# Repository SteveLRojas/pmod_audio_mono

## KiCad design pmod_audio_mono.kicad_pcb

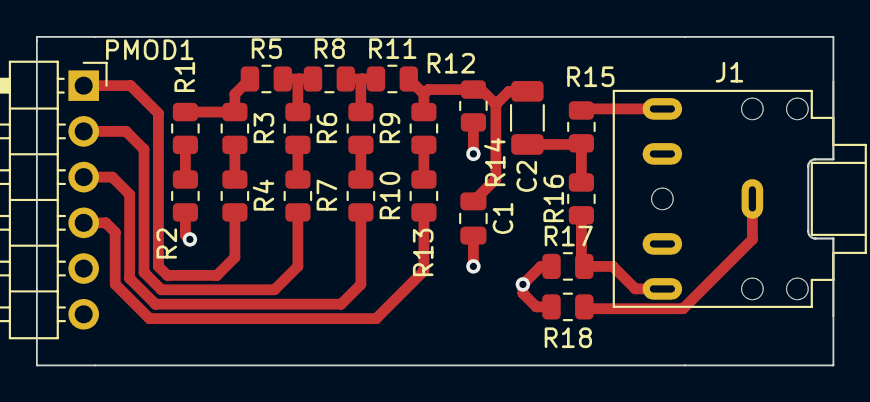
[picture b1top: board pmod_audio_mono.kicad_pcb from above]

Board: 2 copper layers, 44.2 x 18.2 mm, 22 parts (0 on the bottom side), 18 nets.

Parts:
C1: 1n; C_0805_2012Metric
C2: 106; C_1206_3216Metric
J1: AudioJack3_SwitchTR; Jack_3.5mm_CUI_SJ1-3525N_Horizontal
PMOD1: PMOD-Device-x1-Type-1-GPIO; pmod_type_1_pin
R1, R2, R3, R4, R5, R6, R7, R8, R9, R10, R11, R12, R13: 75; R_0805_2012Metric
R14: 1M; R_0805_2012Metric
R15, R16, R17, R18: 0; R_0805_2012Metric

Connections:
GND: C1.2, PMOD1.5 (GND), R2.2, R14.2, R17.1, R18.1
unnamed: C1.1, C2.1, R11.2, R12.1, R14.1
unnamed: C2.2, R15.1, R16.1
unnamed: J1.R, R16.2, R17.2
unnamed: J1.S, R18.2
unnamed: J1.T, R15.2
unnamed: PMOD1.1 (IO0), R4.2
unnamed: PMOD1.2 (IO1), R7.2
unnamed: PMOD1.3 (IO2), R10.2
unnamed: PMOD1.4 (IO3), R13.2
unnamed: R1.1, R3.1, R5.1
unnamed: R1.2, R2.1
unnamed: R3.2, R4.1
unnamed: R5.2, R6.1, R8.1
unnamed: R6.2, R7.1
unnamed: R9.2, R10.1
unnamed: R8.2, R9.1, R11.1
unnamed: R12.2, R13.1

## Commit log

2024-01-21 Added gerber files
